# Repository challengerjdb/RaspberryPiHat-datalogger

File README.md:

# RaspberryPiHat-datalogger

My name is Jacob Bendell, and I’m a student at the University of Pennsylvania studying Electrical Engineering.  I took this past year off from school to avoid online classes and intern at Amped Innovation, a start-up in the Bay Area that designs and builds solar home systems for people in developing countries.  There I worked on a Raspberry Pi project that collects and live-plots voltage, temperature, and battery capacity data.  Additionally, I created a Raspberry Pi hat circuit that enables these data collection features.  

The folder titled 'pythonscript' contains the files to run the data aquisition and live plotter features.  
The folder titled 'kicadhat' contains all the files and libraries for the data logger hat.

Feel free to reach out to me with any questions!
jbendell@seas.upenn.edu

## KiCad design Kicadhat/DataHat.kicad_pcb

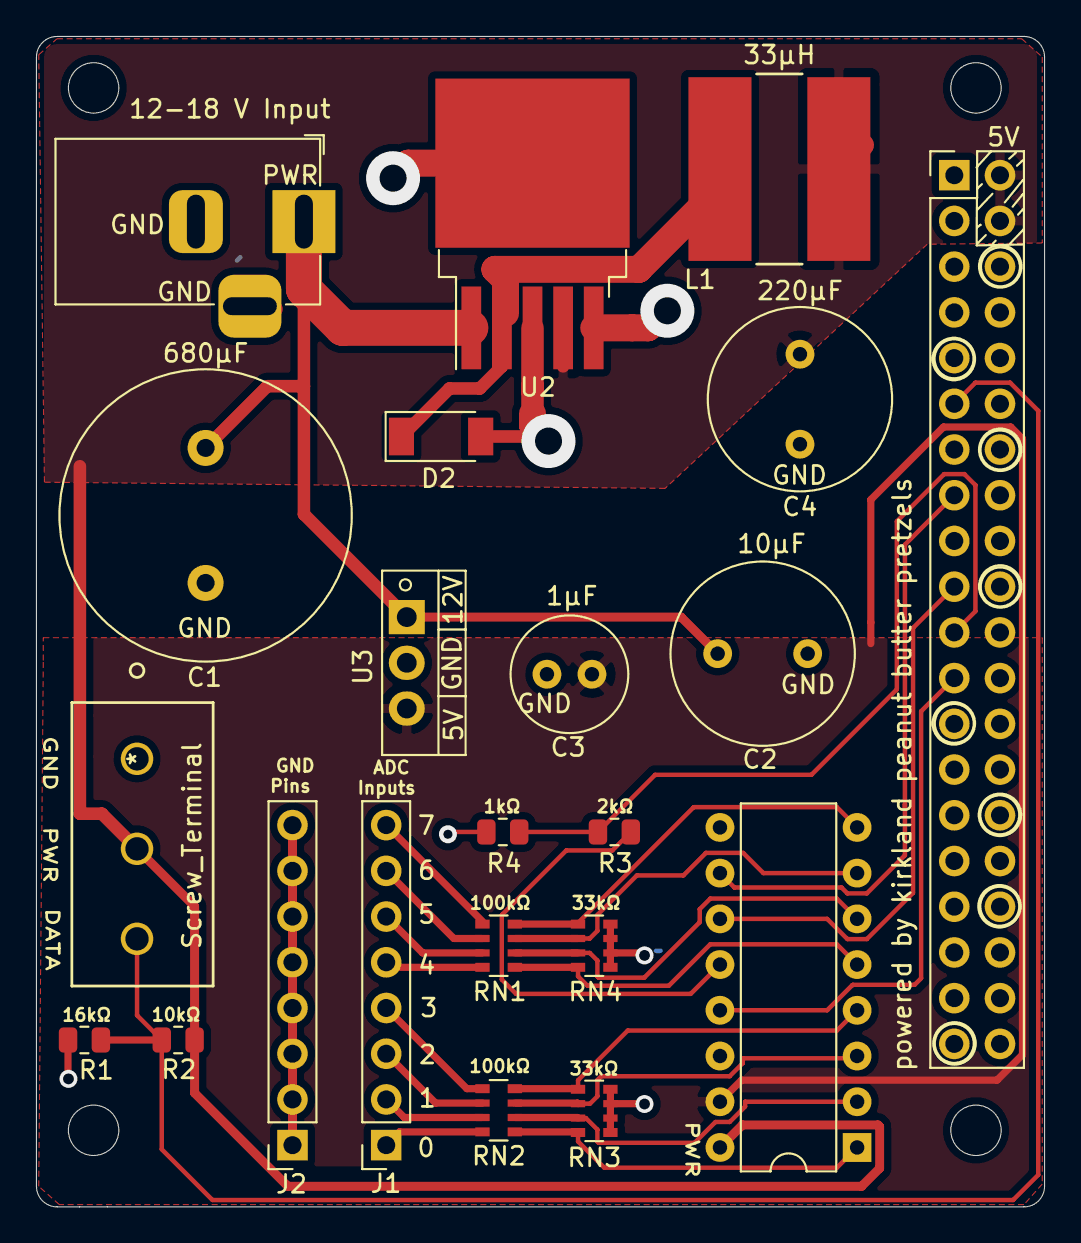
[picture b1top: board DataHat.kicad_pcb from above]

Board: 2 copper layers, 56.0 x 65.0 mm, 22 parts (0 on the bottom side), 27 nets.

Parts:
C1: 680μF; C_Radial_D16.0mm_H25.0mm_P7.50mm
C2: 10μF; C_Radial_D10.0mm_H20.0mm_P5.00mm
C3: 1μF; C_Radial_D6.3mm_H11.0mm_P2.50mm
C4: 220μF; C_Radial_D10.0mm_H20.0mm_P5.00mm
D2: D_Schottky; D_SOD-128
J1, J2: Conn_01x08_Female; PinSocket_1x08_P2.54mm_Vertical
J3: Screw_Terminal; TB002-500-03BE
J5: Raspberry_Pi_2_3; PinHeader_2x20_P2.54mm_Vertical
J6: Barrel_Jack_Switch; BarrelJack_Horizontal
L1: 33μH; SRN1060-330M
R1: 16kΩ; R_0805_2012Metric
R2: 10kΩ; R_0805_2012Metric
R3: 2kΩ; R_0805_2012Metric
R4: 1kΩ; R_0805_2012Metric
RN1, RN2: 100kΩ; R_Array_Convex_4x0603
RN3, RN4: 33kΩ; R_Array_Convex_4x0603
U1: MCP3008; DIP-16_W7.62mm
U2: LM2596S-5; TO-263-5_TabPin3
U3: LM7805_TO220; TO-220-3_Vertical

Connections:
GND: C1.2, C2.2, C3.2, C4.2, D2.2, J2.1, J2.2, J2.3, J2.4, J2.5, J2.6, J2.7, J2.8, J3.1, J5.6, J5.9, J5.14, J5.20, J5.25, J5.30, J5.34, J5.39, J6.2, J6.3, R1.2, R4.2, RN3.5, RN3.6, RN3.7, RN3.8, RN4.5, RN4.6, RN4.7, RN4.8, U1.9, U1.14, U2.3, U2.5, U3.2
unnamed: C1.1, C2.1, J6.1, U2.1, U3.1
unnamed: C3.1, U1.15, U3.3
unnamed: C4.1, J3.2, J5.2, J5.4, L1.2, R2.1, U1.16, U2.4
unnamed: D2.1, L1.1, U2.2
unnamed: J1.1, RN2.4
unnamed: J1.2, RN2.3
unnamed: J1.3, RN2.2
unnamed: J1.4, RN2.1
unnamed: J1.5, RN1.4
unnamed: J1.6, RN1.3
unnamed: J1.7, RN1.2
unnamed: J1.8, RN1.1
unnamed: J3.3, J5.11, R1.1, R2.2
unnamed: J5.15, U1.10
unnamed: J5.19, U1.11
unnamed: J5.21, R3.2, R4.1
unnamed: J5.23, U1.13
unnamed: R3.1, U1.12
unnamed: RN1.5, RN4.4, U1.5
unnamed: RN1.6, RN4.3, U1.6
unnamed: RN1.7, RN4.2, U1.7
unnamed: RN1.8, RN4.1, U1.8
unnamed: RN2.5, RN3.4, U1.1
unnamed: RN2.6, RN3.3, U1.2
unnamed: RN2.7, RN3.2, U1.3
unnamed: RN2.8, RN3.1, U1.4

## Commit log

2021-06-26 Create Kicad Misc
2021-06-28 Create kicadmisc
2021-06-28 Rename start-logging.sh to pythonscript/start-logging.sh
2021-06-28 Rename plotter.py to pythonscript/plotter.py
2021-06-28 Rename main.py to pythonscript/main.py
2021-06-28 Rename dataQ.py to pythonscript/dataQ.py
2021-06-28 Rename R_zigzag.lib to Kicadhat/misc/R_zigzag.lib
2021-06-28 Rename 2-1571552-4.lib to Kicadhat/misc/2-1571552-4.lib
2021-06-28 Rename DataHat to Kicadhat/DataHat
2021-06-28 Rename CUI_TB002-500-03BE.kicad_mod to Kicadhat/misc/CUI_TB002-500-03BE.kicad_mod
2021-06-28 Rename DataHat-cache.lib to Kicadhat/misc/DataHat-cache.lib
2021-06-28 Rename DataHat.xml to Kicadhat/misc/DataHat.xml
2021-06-28 Rename DataHat.sch-bak to Kicadhat/DataHat.sch-bak
2021-06-28 Rename DataHat.kicad_pcb to Kicadhat/DataHat.kicad_pcb
2021-06-28 Rename Kicadhat/DataHat to Kicadhat/Kicadhat/DataHat
2021-06-28 Rename Kicadhat/Kicadhat/DataHat to Kicadhat/DataHat
2021-06-28 Rename DataHat.kicad_pcb-bak to Kicadhat/DataHat.kicad_pcb-bak
2021-06-28 Rename DataHat.net to Kicadhat/DataHat.net
2021-06-28 Rename DataHat.pro to Kicadhat/DataHat.pro
2021-06-28 Rename DataHat.sch to Kicadhat/DataHat.sch

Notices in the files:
parts and their libraries:
Copyright 2016 Accelerated Designs. All rights reserved.
